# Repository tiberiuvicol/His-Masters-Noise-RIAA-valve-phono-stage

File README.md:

# His Master's Noise a high quality RIAA valve phono stage

This is a simple PCB designed in KiCad for His Master's Noise phono stage.</br>
https://www.diyaudio.com/community/threads/his-masters-noise-a-thoroughly-modern-tube-phono-preamp.163570/</br>
PCB's are for power supply and separate left/right channels.</br>
Install KiCad, download project, open HMN.kicad_pro and hmn_ps.kicad_pro

</br>

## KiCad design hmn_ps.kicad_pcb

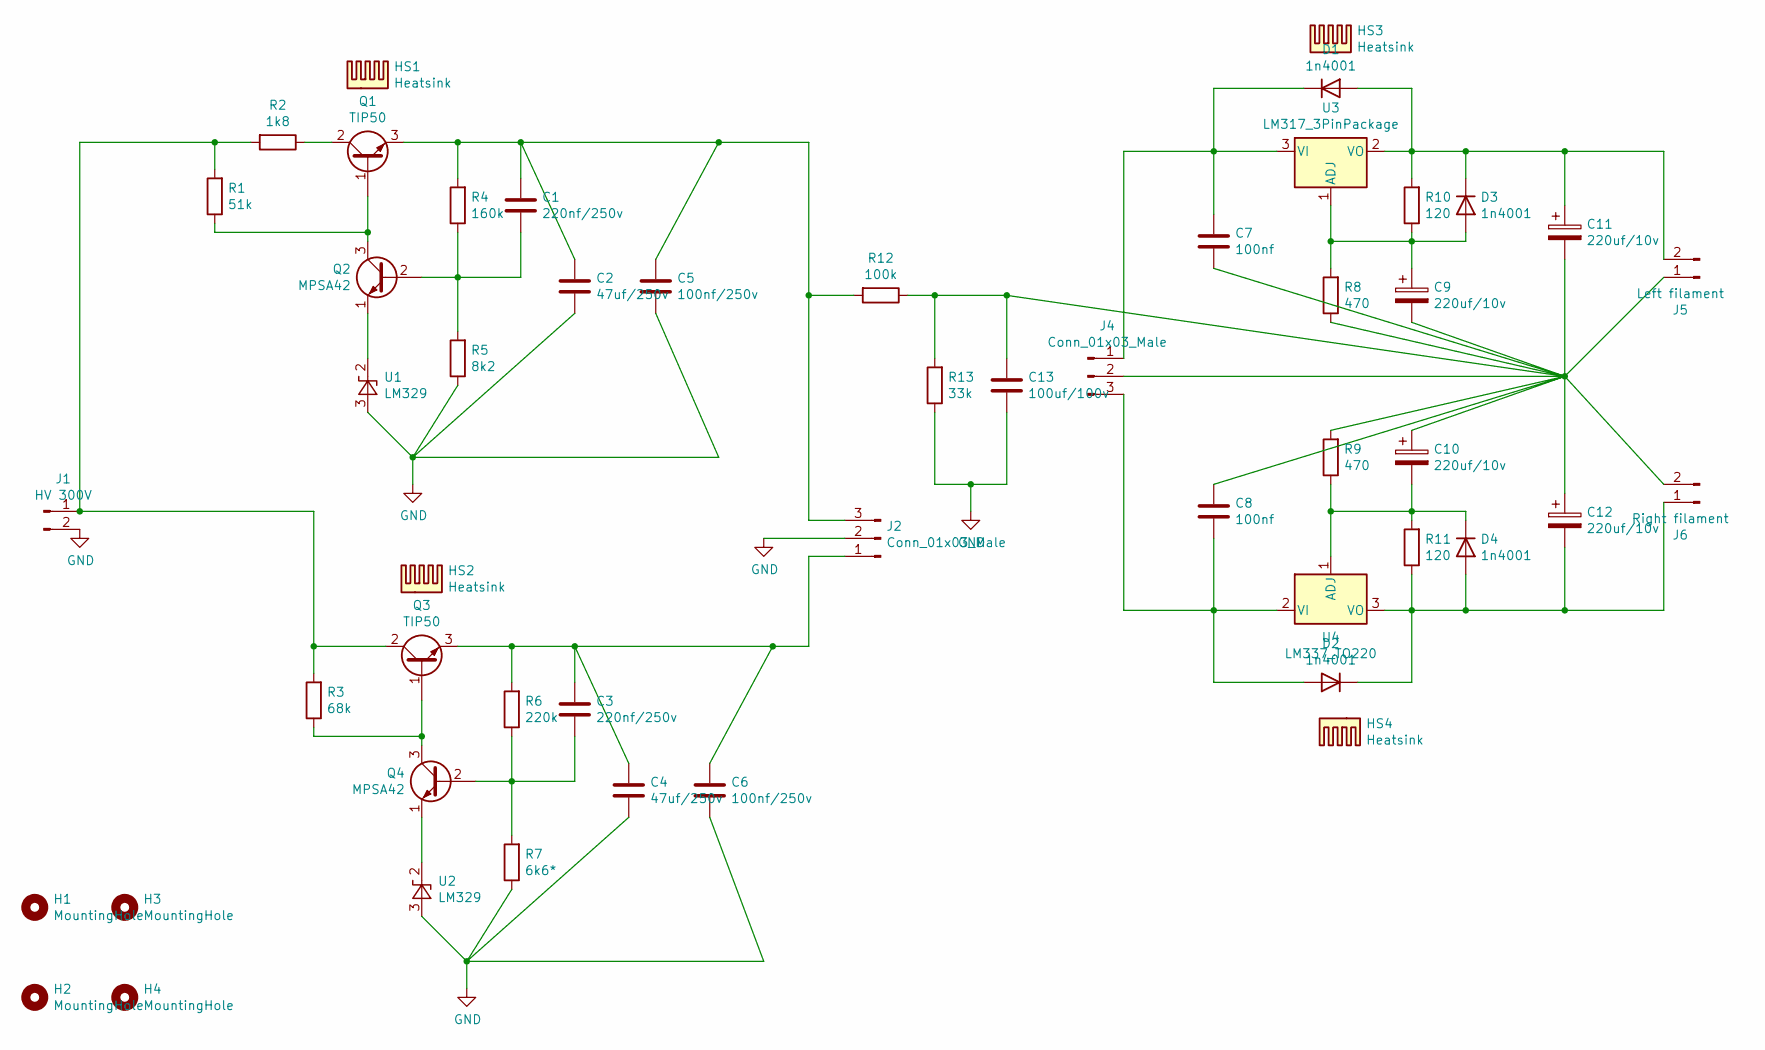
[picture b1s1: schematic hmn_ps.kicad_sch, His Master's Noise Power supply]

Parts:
C1, C3: 220nf/250v; C_Rect_L13.0mm_W6.0mm_P10.00mm_FKS3_FKP3_MKS4
C2, C4: 47uf/250v; CP_Radial_D18.0mm_P7.50mm
C5, C6: 100nf/250v; C_Rect_L13.0mm_W4.0mm_P10.00mm_FKS3_FKP3_MKS4
C7, C8: 100nf; C_Rect_L7.5mm_W6.5mm_P5.00mm
C9, C10, C11, C12: 220uf/10v; C_Radial_D6.3mm_H11.0mm_P2.50mm
C13: 100uf/100v; CP_Radial_D18.0mm_P7.50mm
D1, D2, D3, D4: 1n4001; D_DO-41_SOD81_P7.62mm_Horizontal
H1, H2, H3, H4: MountingHole; MountingHole_3.2mm_M3_Pad_Via
HS1, HS2: Heatsink; Heatsink_Fischer_SK104-STC-STIC_35x13mm_2xDrill2.5mm
HS3, HS4: Heatsink; Heatsink_Fischer_SK129-STS_42x25mm_2xDrill2.5mm
J1: HV 300V; TerminalBlock_Altech_AK300-2_P5.00mm
J2, J4: Conn_01x03_Male; TerminalBlock_Altech_AK300-3_P5.00mm
J5: Left filament; TerminalBlock_Altech_AK300-2_P5.00mm
J6: Right filament; TerminalBlock_Altech_AK300-2_P5.00mm
Q1, Q3: TIP50; TO-220-3_Vertical
Q2, Q4: MPSA42; TO-92_Inline
R1: 51k; R_Axial_DIN0207_L6.3mm_D2.5mm_P10.16mm_Horizontal
R2: 1k8; R_Axial_DIN0414_L11.9mm_D4.5mm_P20.32mm_Horizontal
R3: 68k; R_Axial_DIN0207_L6.3mm_D2.5mm_P10.16mm_Horizontal
R4: 160k; R_Axial_DIN0207_L6.3mm_D2.5mm_P10.16mm_Horizontal
R5: 8k2; R_Axial_DIN0207_L6.3mm_D2.5mm_P10.16mm_Horizontal
R6: 220k; R_Axial_DIN0207_L6.3mm_D2.5mm_P10.16mm_Horizontal
R7: 6k6*; R_Axial_DIN0207_L6.3mm_D2.5mm_P10.16mm_Horizontal
R8, R9: 470; R_Axial_DIN0207_L6.3mm_D2.5mm_P10.16mm_Horizontal
R10, R11: 120; R_Axial_DIN0207_L6.3mm_D2.5mm_P10.16mm_Horizontal
R12: 100k; R_Axial_DIN0414_L11.9mm_D4.5mm_P20.32mm_Horizontal
R13: 33k; R_Axial_DIN0207_L6.3mm_D2.5mm_P10.16mm_Horizontal
U1, U2: LM329; TO-92_Inline_Wide
U3: LM317_3PinPackage; TO-220F-3_Vertical
U4: LM337_TO220; TO-220F-3_Vertical

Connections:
GND: C2.2, C4.2, C5.2, C6.2, C13.2, J1.2, J2.2, R5.1, R7.1, R13.1, U1.3 (A), U2.3 (A)
unnamed: C1.1, C2.1, C5.1, J2.3, Q1.3 (E), R4.2, R12.2
unnamed: C1.2, Q2.2 (B), R4.1, R5.2
unnamed: C3.1, C4.1, C6.1, J2.1, Q3.3 (E), R6.2
unnamed: C3.2, Q4.2 (B), R6.1, R7.2
unnamed: C7.1, D1.1 (K), J4.1, U3.3 (VI)
unnamed: C8.2, D2.2 (A), J4.3, U4.2 (VI)
unnamed: C9.1, D3.2 (A), R8.2, R10.1, U3.1 (ADJ)
unnamed: C7.2, C8.1, C9.2, C10.1, C11.2, C12.1, C13.1, J4.2, J5.1, J6.2, R8.1, R9.2, R12.1, R13.2
unnamed: C10.2, D4.1 (K), R9.1, R11.2, U4.1 (ADJ)
unnamed: C11.1, D1.2 (A), D3.1 (K), J5.2, R10.2, U3.2 (VO)
unnamed: C12.2, D2.1 (K), D4.2 (A), J6.1, R11.1, U4.3 (VO)
unnamed: J1.1, Q3.2 (C), R1.2, R2.2, R3.2
unnamed: Q1.1 (B), Q2.3 (C), R1.1
unnamed: Q1.2 (C), R2.1
unnamed: Q2.1 (E), U1.2 (K)
unnamed: Q3.1 (B), Q4.3 (C), R3.1
unnamed: Q4.1 (E), U2.2 (K)

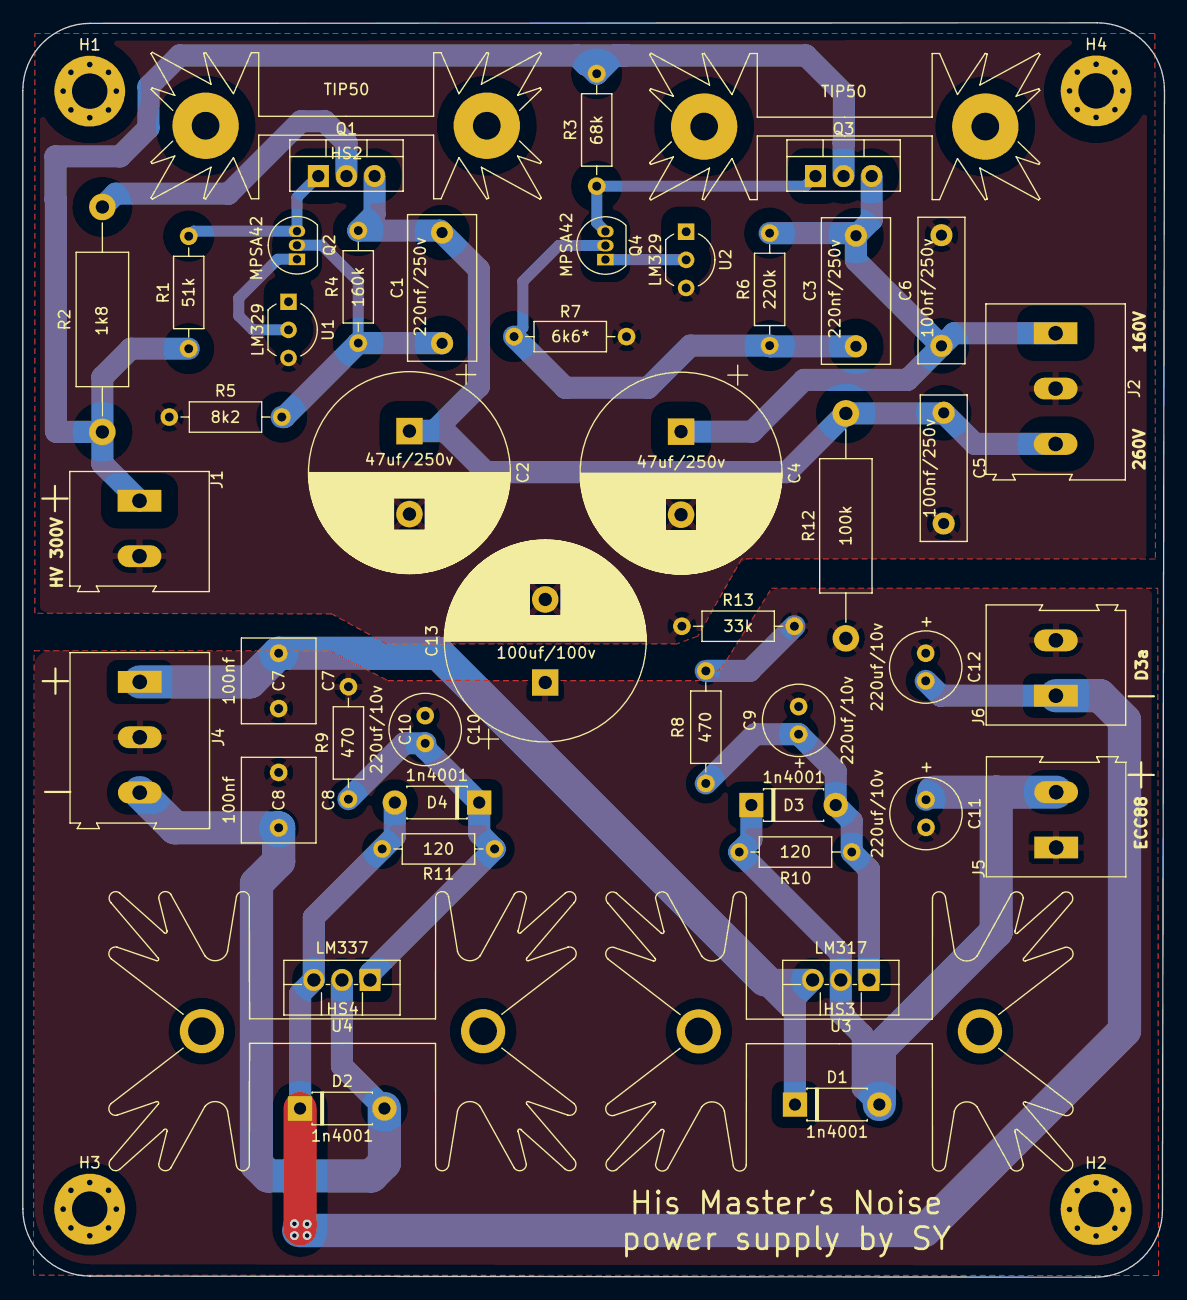
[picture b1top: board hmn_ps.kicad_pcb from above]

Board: 2 copper layers, 103.1 x 113.3 mm, 51 parts (0 on the bottom side), 18 nets.

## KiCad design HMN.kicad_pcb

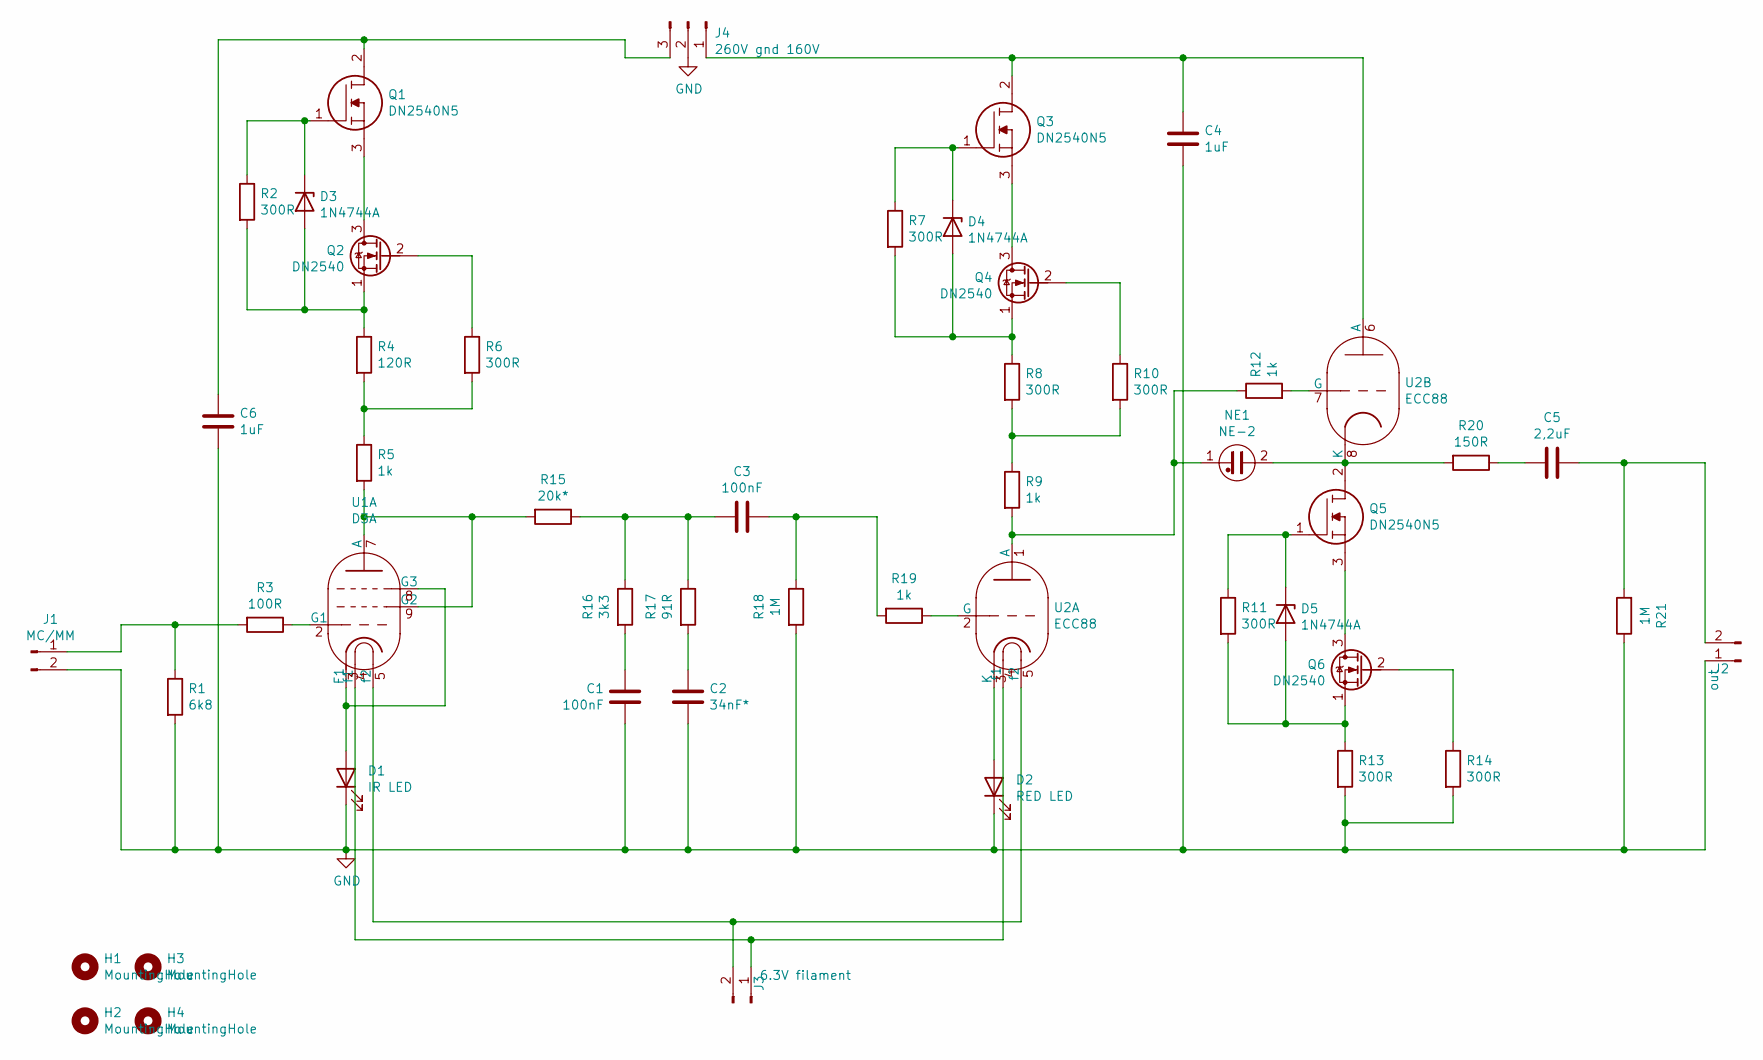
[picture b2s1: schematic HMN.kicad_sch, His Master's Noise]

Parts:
C1, C3: 100nF; C_Rect_L16.5mm_W7.3mm_P15.00mm_MKT
C2: 34nF*; C_Rect_L16.5mm_W7.3mm_P15.00mm_MKT
C4, C6: 1uF; C_Rect_L31.5mm_W20.0mm_P27.50mm_MKS4
C5: 2,2uF; C_Rect_L31.5mm_W20.0mm_P27.50mm_MKS4
D1: IR LED; LED_D3.0mm_IRBlack
D2: RED LED; LED_D3.0mm_IRGrey
D3, D4, D5: 1N4744A; D_DO-41_SOD81_P10.16mm_Horizontal
H1, H2, H3, H4: MountingHole; MountingHole_3.2mm_M3_Pad_Via
J1: MC/MM; TerminalBlock_Altech_AK300-2_P5.00mm
J2: out; TerminalBlock_Altech_AK300-2_P5.00mm
J3: 6.3V filament; TerminalBlock_Altech_AK300-2_P5.00mm
J4: 260V gnd 160V; TerminalBlock_Altech_AK300-3_P5.00mm
NE1: NE-2; LED_D5.0mm
Q1, Q3, Q5: DN2540N5; TO254P483X1016X2375-3P; Mouser Part Number 689-DN2540N5
Q2, Q4, Q6: DN2540; TO-92L_Inline_Wide
R1: 6k8; R_Axial_DIN0207_L6.3mm_D2.5mm_P10.16mm_Horizontal
R2, R6, R7, R8, R10, R11, R13, R14: 300R; R_Axial_DIN0207_L6.3mm_D2.5mm_P10.16mm_Horizontal
R3: 100R; R_Axial_DIN0207_L6.3mm_D2.5mm_P10.16mm_Horizontal
R4: 120R; R_Axial_DIN0207_L6.3mm_D2.5mm_P10.16mm_Horizontal
R5, R9, R12, R19: 1k; R_Axial_DIN0207_L6.3mm_D2.5mm_P10.16mm_Horizontal
R15: 20k*; R_Axial_DIN0207_L6.3mm_D2.5mm_P10.16mm_Horizontal
R16: 3k3; R_Axial_DIN0207_L6.3mm_D2.5mm_P10.16mm_Horizontal
R17: 91R; R_Axial_DIN0207_L6.3mm_D2.5mm_P10.16mm_Horizontal
R18, R21: 1M; R_Axial_DIN0207_L6.3mm_D2.5mm_P10.16mm_Horizontal
R20: 150R; R_Axial_DIN0207_L6.3mm_D2.5mm_P10.16mm_Horizontal
U1: D3A; Valve_ECC-83-2
U2: ECC88; Valve_ECC-83-2

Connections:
GND: C1.1, C2.1, C4.2, C6.2, D1.1 (K), D2.1 (K), J1.2, J2.1, J4.2, R1.2, R13.2, R14.2, R18.2, R21.1; also elsewhere on the board
unnamed 1: C1.2, R16.2; also elsewhere on the board
unnamed: C2.2, R17.2
unnamed 3: C3.1, R15.1, R16.1, R17.1; also elsewhere on the board
unnamed 4: C3.2, R18.1, R19.2; also elsewhere on the board
unnamed: C4.1, J4.1, Q3.2, U2.6 (A)
unnamed: C5.1, J2.2, R21.2
unnamed: C5.2, R20.1
unnamed: C6.1, J4.3, Q1.2
unnamed: D1.2 (A), U1.3 (F1), U1.8 (G3)
unnamed: D2.2 (A), U2.3 (K)
unnamed: D3.1 (K), Q1.1, R2.1
unnamed: D3.2 (A), Q2.1 (S), R2.2, R4.1
unnamed: D4.1 (K), Q3.1, R7.1
unnamed: D4.2 (A), Q4.1 (S), R7.2, R8.1
unnamed: D5.1 (K), Q5.1, R11.1
unnamed: D5.2 (A), Q6.1 (S), R11.2, R13.1
unnamed 17: J1.1, R1.1, R3.2; also elsewhere on the board
unnamed: J3.1, U1.4 (f1), U2.4 (f1)
unnamed: J3.2, U1.5 (f2), U2.5 (f2)
unnamed: NE1.1, R9.2, R12.1, U2.1 (A)
unnamed: NE1.2, Q5.2, R20.2, U2.8 (K)
unnamed: Q1.3, Q2.3 (D)
unnamed: Q2.2 (G), R6.1
unnamed: Q3.3, Q4.3 (D)
unnamed: Q4.2 (G), R10.1
unnamed: Q5.3, Q6.3 (D)
unnamed: Q6.2 (G), R14.1
unnamed: R3.1, U1.2 (G1)
unnamed: R4.2, R5.1, R6.2
unnamed: R8.2, R9.1, R10.2
unnamed: R12.2, U2.7 (G)
unnamed: R5.2, R15.2, U1.7 (A), U1.9 (G2)
unnamed: R19.1, U2.2 (G)

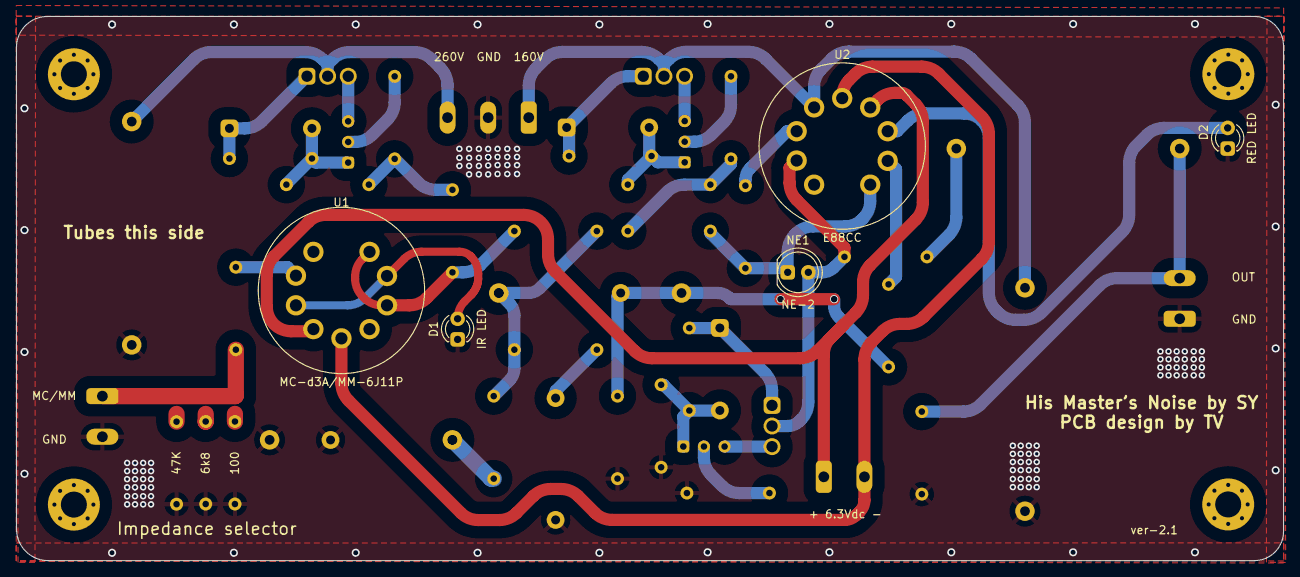
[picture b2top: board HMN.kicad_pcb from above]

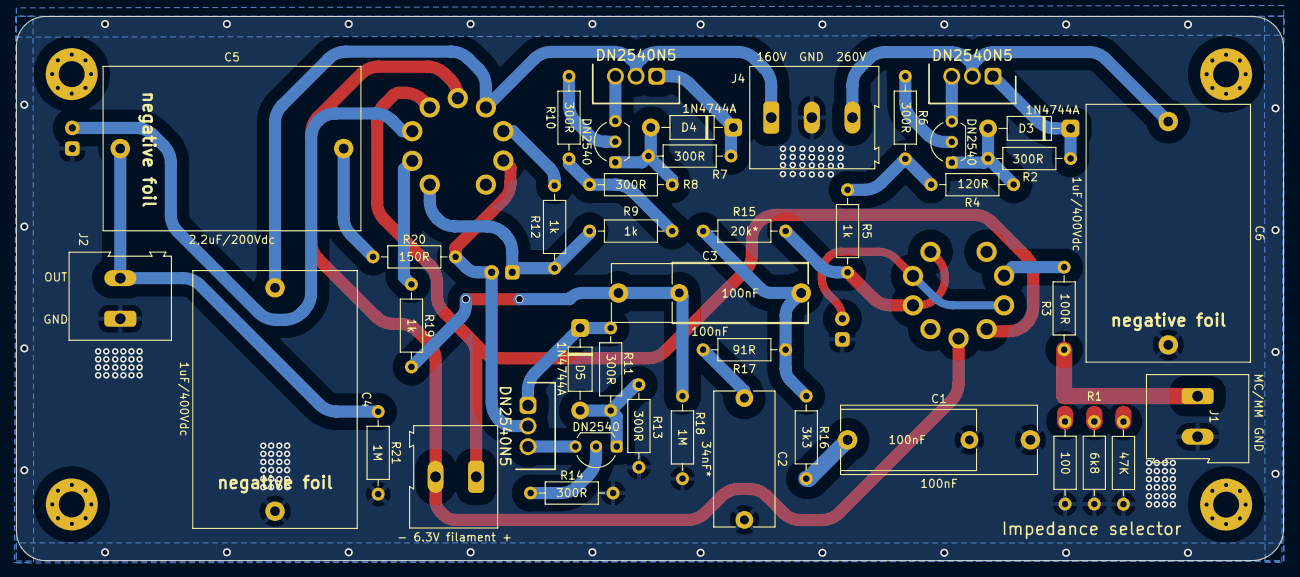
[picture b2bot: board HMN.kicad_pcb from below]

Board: 2 copper layers, 156.0 x 67.0 mm, 53 parts (44 on the bottom side), 34 nets.

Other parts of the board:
C1#2: 100nF; C_Rect_L24.0mm_W8.3mm_P22.50mm_MKT
C3#2: 100nF; C_Rect_L24.0mm_W7.0mm_P22.50mm_MKT
R1#2: 100; R_Axial_DIN0207_L6.3mm_D2.5mm_P10.16mm_Horizontal
R1#3: 6k8; R_Axial_DIN0207_L6.3mm_D2.5mm_P10.16mm_Horizontal

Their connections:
GND: C1#2.1, R1#2.2, R1#3.2; also elsewhere on the board
unnamed 1: C1#2.2; also elsewhere on the board
unnamed 3: C3#2.1; also elsewhere on the board
unnamed 4: C3#2.2; also elsewhere on the board
unnamed 17: R1#2.1, R1#3.1; also elsewhere on the board

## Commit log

2023-04-16 Create Power supply
